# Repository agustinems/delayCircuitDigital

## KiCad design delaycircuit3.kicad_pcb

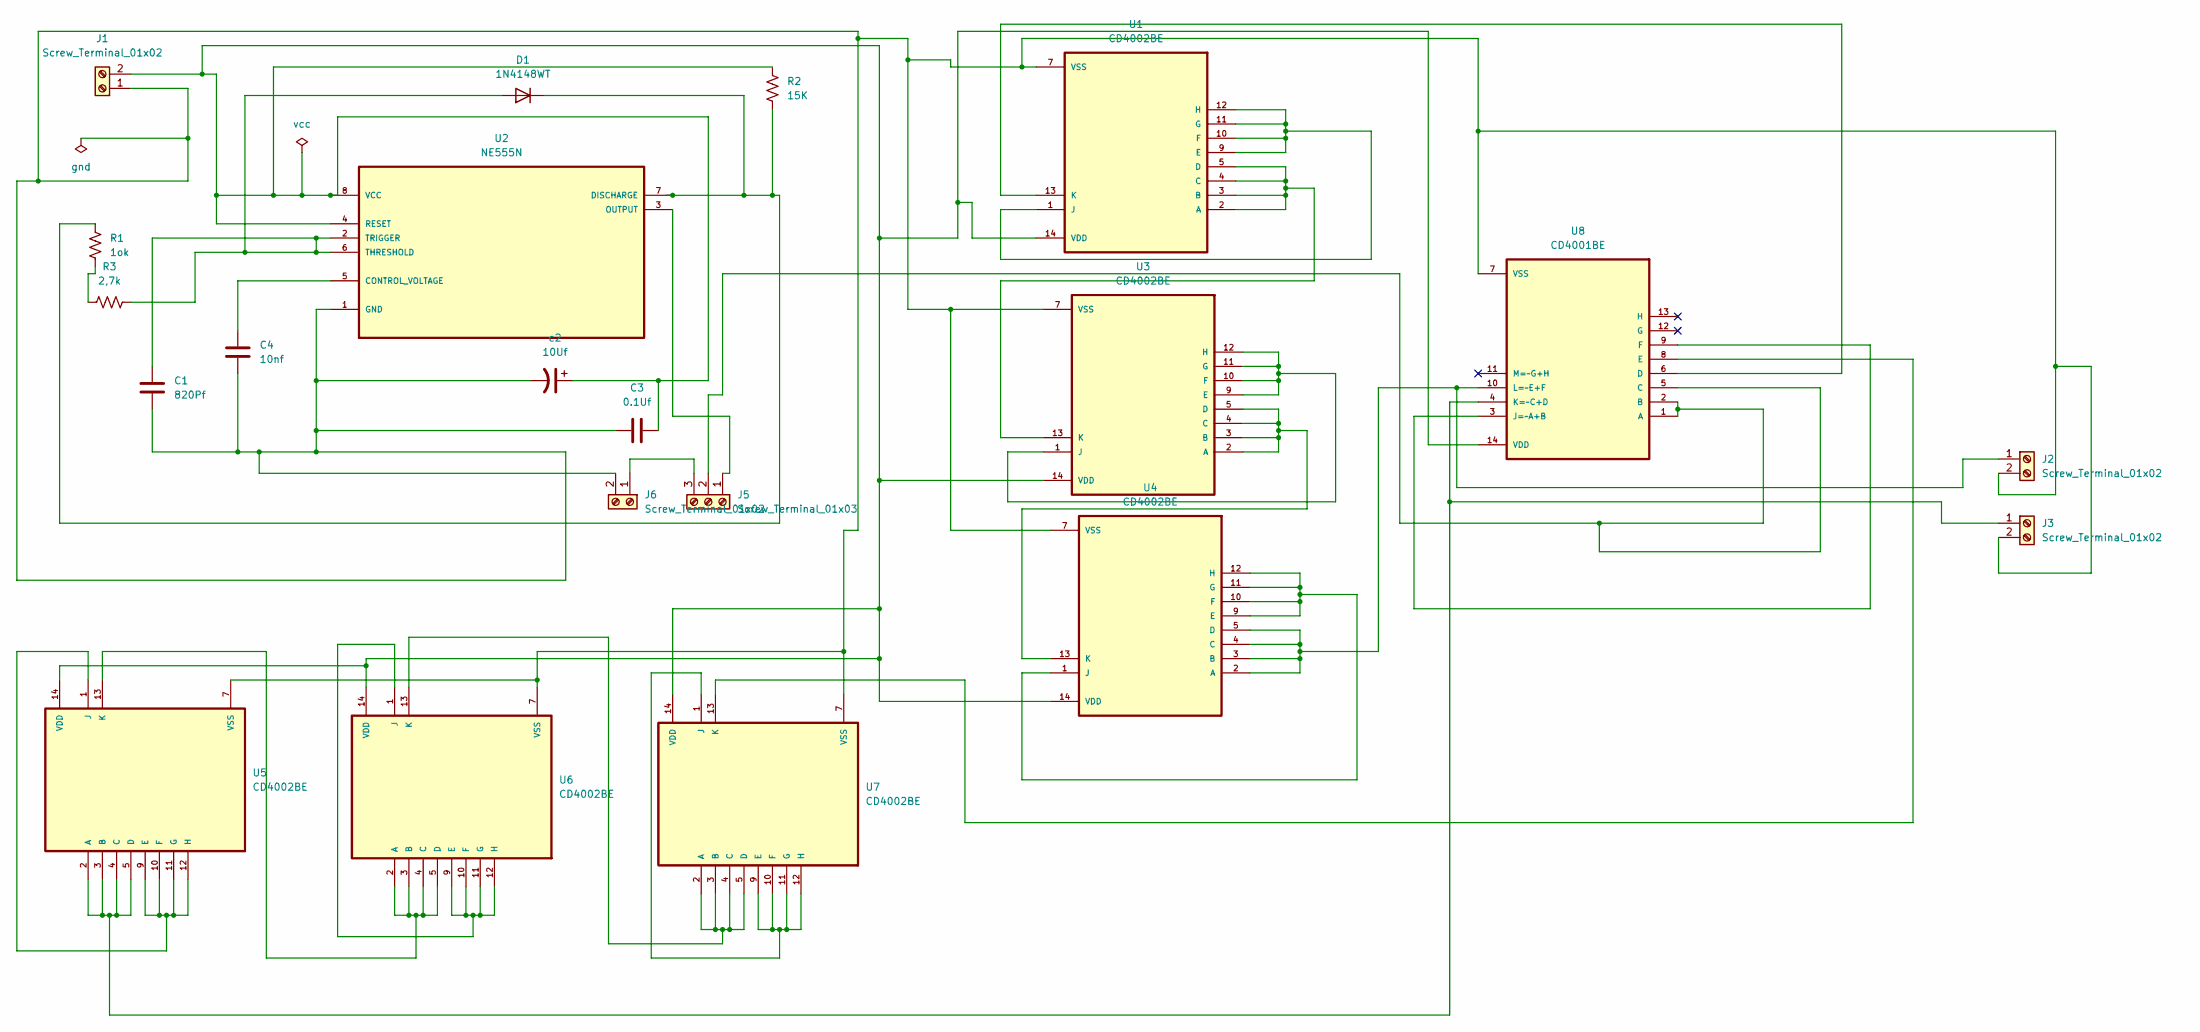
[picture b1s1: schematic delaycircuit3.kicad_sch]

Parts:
C1: 820Pf; C_Disc_D5.1mm_W3.2mm_P5.00mm
C3: 0.1Uf; C_Disc_D5.1mm_W3.2mm_P5.00mm
C4: 10nf; C_Disc_D5.1mm_W3.2mm_P5.00mm
D1: 1N4148WT; D_T-1_P10.16mm_Horizontal
J1, J2, J3, J6: Screw_Terminal_01x02; TerminalBlock_Phoenix_MKDS-1,5-2-5.08_1x02_P5.08mm_Horizont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
J5: Screw_Terminal_01x03; TerminalBlock_Phoenix_MKDS-1,5-3-5.08_1x03_P5.08mm_Horizont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
R1: 1ok; R_Axial_DIN0204_L3.6mm_D1.6mm_P1.90mm_Vertical
R2: 15K; R_Axial_DIN0204_L3.6mm_D1.6mm_P1.90mm_Vertical
R3: 2,7k; R_Axial_DIN0204_L3.6mm_D1.6mm_P7.62mm_Horizontal
U1, U3, U4, U5, U6, U7: CD4002BE; DIP794W45P254L1969H508Q14
U2: NE555N; DIP254P762X533-8; MPN NE555N
U8: CD4001BE; DIP794W45P254L1969H508Q14
c2: 10Uf; CP_Radial_D6.3mm_P2.50mm

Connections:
unnamed: C1.1, D1.2 (A), R3.2, U2.2 (TRIGGER), U2.6 (THRESHOLD)
unnamed: D1.1 (K), R1.2, R2.1, U2.7 (DISCHARGE)
unnamed: C1.2, C3.1, C4.2, J1.1, J2.2, J3.2, J6.2, U1.7 (VSS), U2.1 (GND), U3.7 (VSS), U4.7 (VSS), U5.7 (VSS), U6.7 (VSS), U7.7 (VSS), U8.7 (VSS), c2.2
unnamed: C3.2, J1.2, R2.2, U1.14 (VDD), U2.4 (RESET), U2.8 (VCC), U3.14 (VDD), U4.14 (VDD), U5.14 (VDD), U6.14 (VDD), U7.14 (VDD), U8.14 (VDD), c2.1
unnamed: J2.1, U4.2 (A), U4.3 (B), U4.4 (C), U4.5 (D), U8.10 (L=~E+F)
unnamed: J3.1, U5.2 (A), U5.3 (B), U5.4 (C), U5.5 (D), U8.4 (K=~C+D)
unnamed: J5.1, U2.3 (OUTPUT)
unnamed: J5.2, U8.1 (A), U8.2 (B), U8.5 (C)
unnamed: J5.3, J6.1
unnamed: R1.1, R3.1
unnamed: U1.2 (A), U1.3 (B), U1.4 (C), U1.5 (D), U3.13 (K)
unnamed: U1.1 (J), U1.9 (E), U1.10 (F), U1.11 (G), U1.12 (H)
unnamed: U1.13 (K), U8.6 (D)
unnamed: C4.1, U2.5 (CONTROL_VOLTAGE)
unnamed: U3.2 (A), U3.3 (B), U3.4 (C), U3.5 (D), U4.13 (K)
unnamed: U3.1 (J), U3.9 (E), U3.10 (F), U3.11 (G), U3.12 (H)
unnamed: U4.1 (J), U4.9 (E), U4.10 (F), U4.11 (G), U4.12 (H)
unnamed: U5.1 (J), U5.9 (E), U5.10 (F), U5.11 (G), U5.12 (H)
unnamed: U5.13 (K), U6.2 (A), U6.3 (B), U6.4 (C), U6.5 (D)
unnamed: U6.1 (J), U6.9 (E), U6.10 (F), U6.11 (G), U6.12 (H)
unnamed: U6.13 (K), U7.2 (A), U7.3 (B), U7.4 (C), U7.5 (D)
unnamed: U7.1 (J), U7.9 (E), U7.10 (F), U7.11 (G), U7.12 (H)
unnamed: U7.13 (K), U8.8 (E)
unnamed: U8.3 (J=~A+B), U8.9 (F)

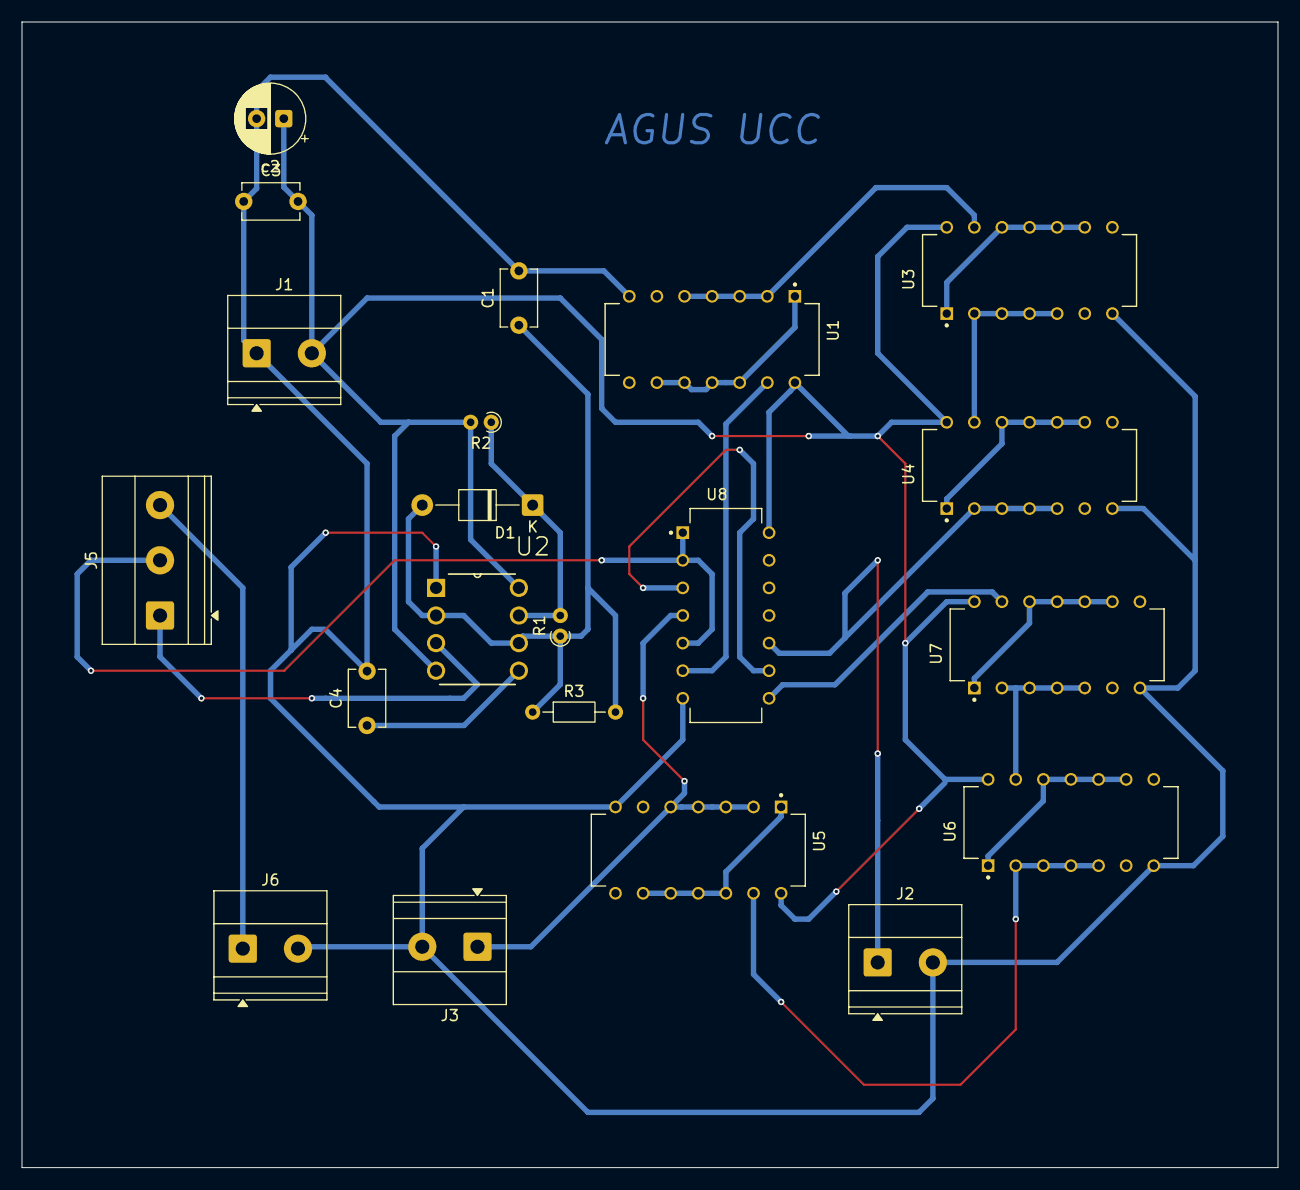
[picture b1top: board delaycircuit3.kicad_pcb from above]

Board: 2 copper layers, 115.6 x 105.4 mm, 21 parts (0 on the bottom side), 24 nets.

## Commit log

2026-04-15 rooteo 15-04
2026-04-17 resistencia en seire
